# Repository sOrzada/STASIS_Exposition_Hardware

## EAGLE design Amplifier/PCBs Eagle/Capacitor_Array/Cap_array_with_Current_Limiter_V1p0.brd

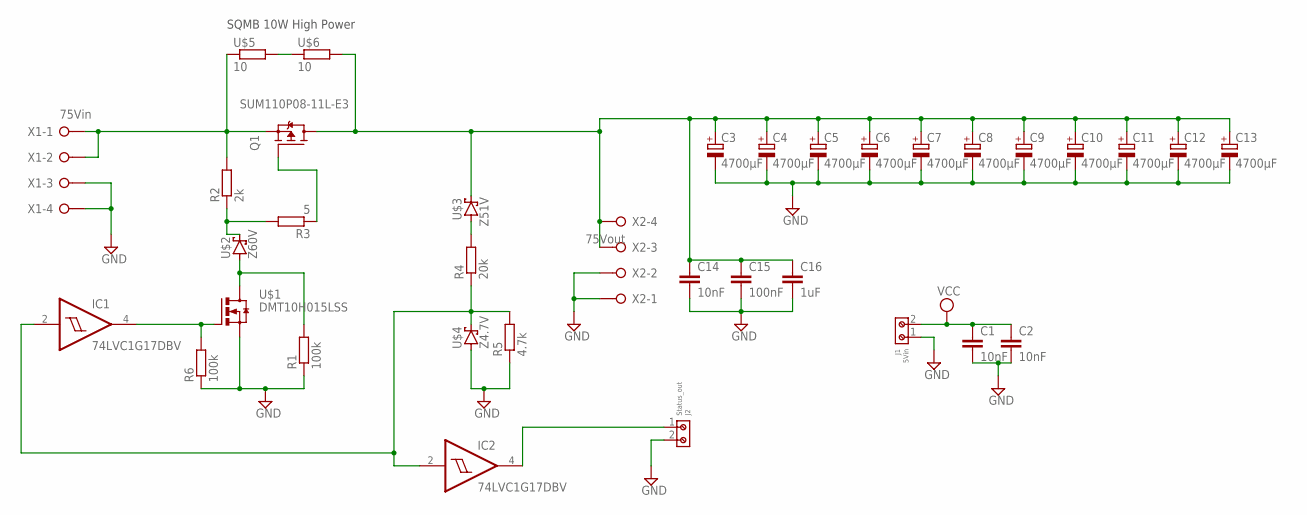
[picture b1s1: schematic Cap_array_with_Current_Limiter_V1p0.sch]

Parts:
C1, C2: 10nF; C0805
C3, C4, C5, C6, C7, C8, C9, C10, C11, C12, C13: 4700µF; EB30D
C14: 10nF; C1206
C15: 100nF; C1206
C16: 1uF; C1206
IC1, IC2: 74LVC1G17DBV; SOT23-5
J1: 5Vin; 691210910002
J2: Status_out; 691210910002
Q1: SUM110P08-11L-E3; TO263
R1, R6: 100k; R0805
R2: 2k; R2512
R3: 5; R0805
R4: 20k; R0805
R5: 4.7k; R0805
U$1: DMT10H015LSS; SOIC8
U$2: Z60V; DO-214AA
U$3: Z51V; DO-214AA
U$4: Z4.7V; DO-214AA
U$5, U$6: 10; SQMB
X1: 75Vin; W237-4P
X2: 75Vout; W237-4P

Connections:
GND: C1.2, C2.2, C3.-, C4.-, C5.-, C6.-, C7.-, C8.-, C9.-, C10.-, C11.-, C12.-, C13.-, C14.2, C15.2, C16.2, IC1.3 (GND), IC2.3 (GND), J1.1, J2.2, R1.1, R5.1, R6.1, U$1.1 (S), U$1.2 (S), U$1.3 (S), U$4.A, X1.3, X1.4, X2.1, X2.2
unnamed: R2.1, R3.2, U$2.C
unnamed: Q1.2 (S), R2.2, U$5.P$1 (1), X1.1, X1.2
unnamed: U$5.P$2 (2), U$6.P$1 (1)
unnamed: IC1.4 (O), R6.2, U$1.4 (G)
unnamed: Q1.1 (G), R3.1
unnamed: C3.+, C4.+, C5.+, C6.+, C7.+, C8.+, C9.+, C10.+, C11.+, C12.+, C13.+, C14.1, C15.1, C16.1, Q1.3 (D), U$3.C, U$6.P$2 (2), X2.3, X2.4
unnamed: R4.2, U$3.A
unnamed: IC1.2 (I), IC2.2 (I), R4.1, R5.2, U$4.C
unnamed: IC2.4 (O), J2.1
unnamed: R1.2, U$1.5 (D), U$1.6 (D), U$1.7 (D), U$1.8 (D), U$2.A
VCC: C1.1, C2.1, IC1.5 (VCC), IC2.5 (VCC), J1.2

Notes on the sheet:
SQMB 10W High Power

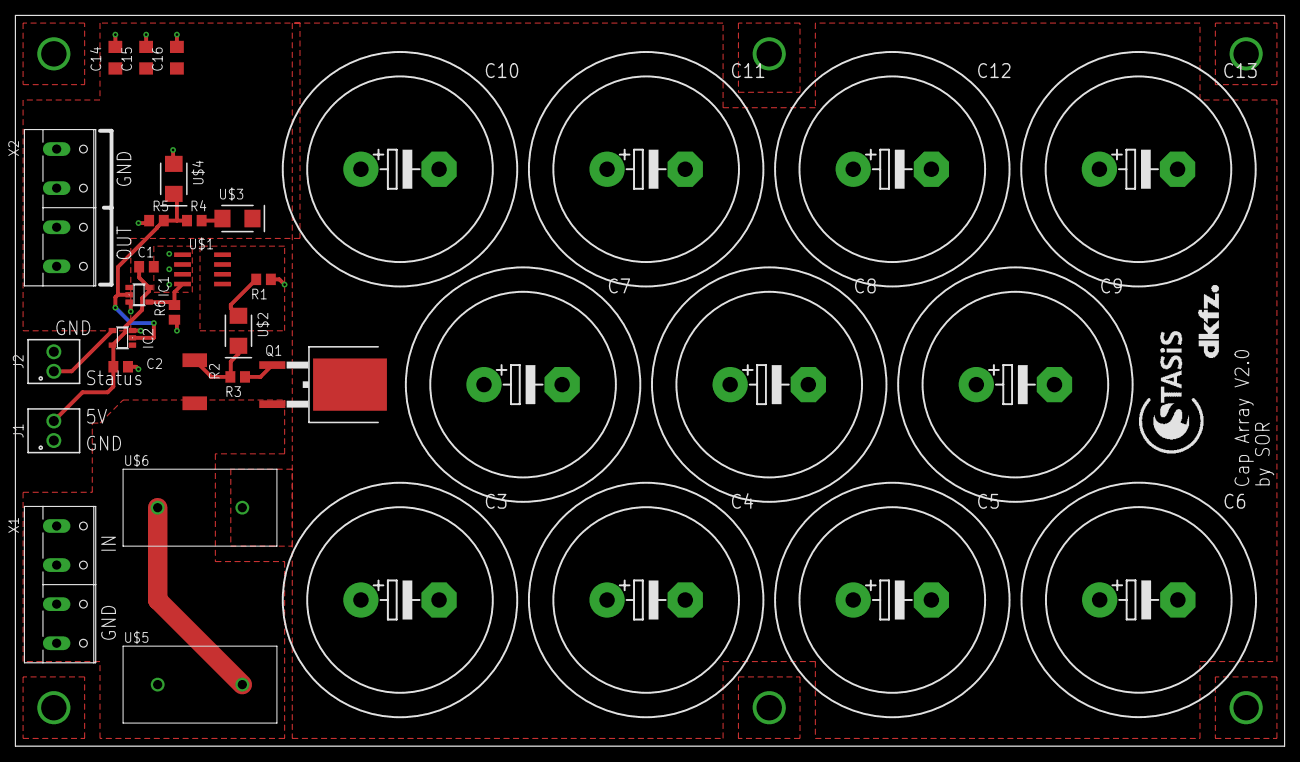
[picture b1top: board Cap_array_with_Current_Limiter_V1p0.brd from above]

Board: 2 copper layers, 165.0 x 95.0 mm, 37 parts (0 on the bottom side), 12 nets.

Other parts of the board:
U$7: LOGO_STASIS
U$8: LOGO_DKFZ

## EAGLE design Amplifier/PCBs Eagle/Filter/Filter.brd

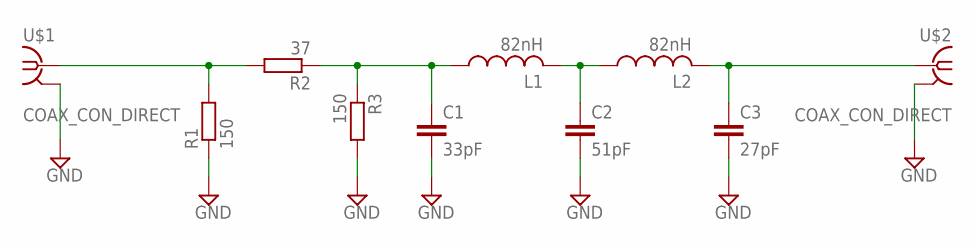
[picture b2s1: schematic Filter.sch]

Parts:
C1: 33pF; C0805
C2: 51pF; C0805
C3: 27pF; C0805
L1, L2: 82nH; L2012C
R1, R3: 150; R0805
R2: 37; R0805
U$1, U$2: COAX_CON_DIRECT; COAX.141

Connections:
GND: C1.2, C2.2, C3.2, R1.1, R3.2, U$1.P$2 (GND), U$2.P$2 (GND)
unnamed: C3.1, L2.2, U$2.P$1 (1)
unnamed: C2.1, L1.2, L2.1
unnamed: C1.1, L1.1, R2.1, R3.1
unnamed: R1.2, R2.2, U$1.P$1 (1)

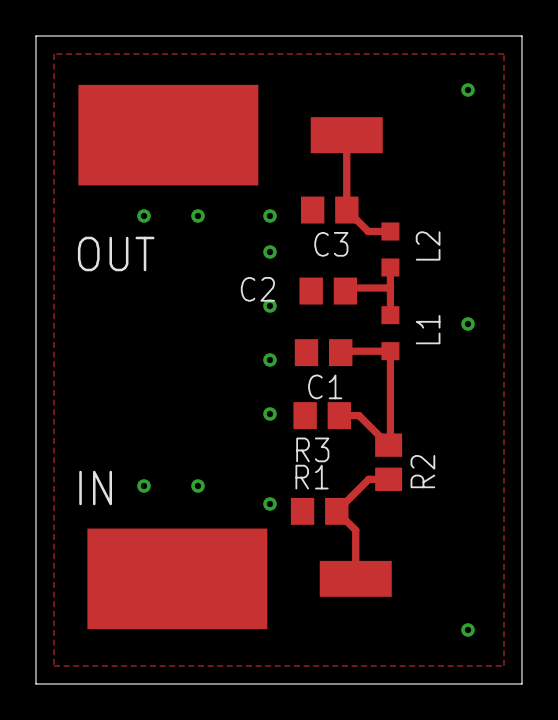
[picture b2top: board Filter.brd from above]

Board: 2 copper layers, 27.0 x 36.0 mm, 10 parts (0 on the bottom side), 5 nets.

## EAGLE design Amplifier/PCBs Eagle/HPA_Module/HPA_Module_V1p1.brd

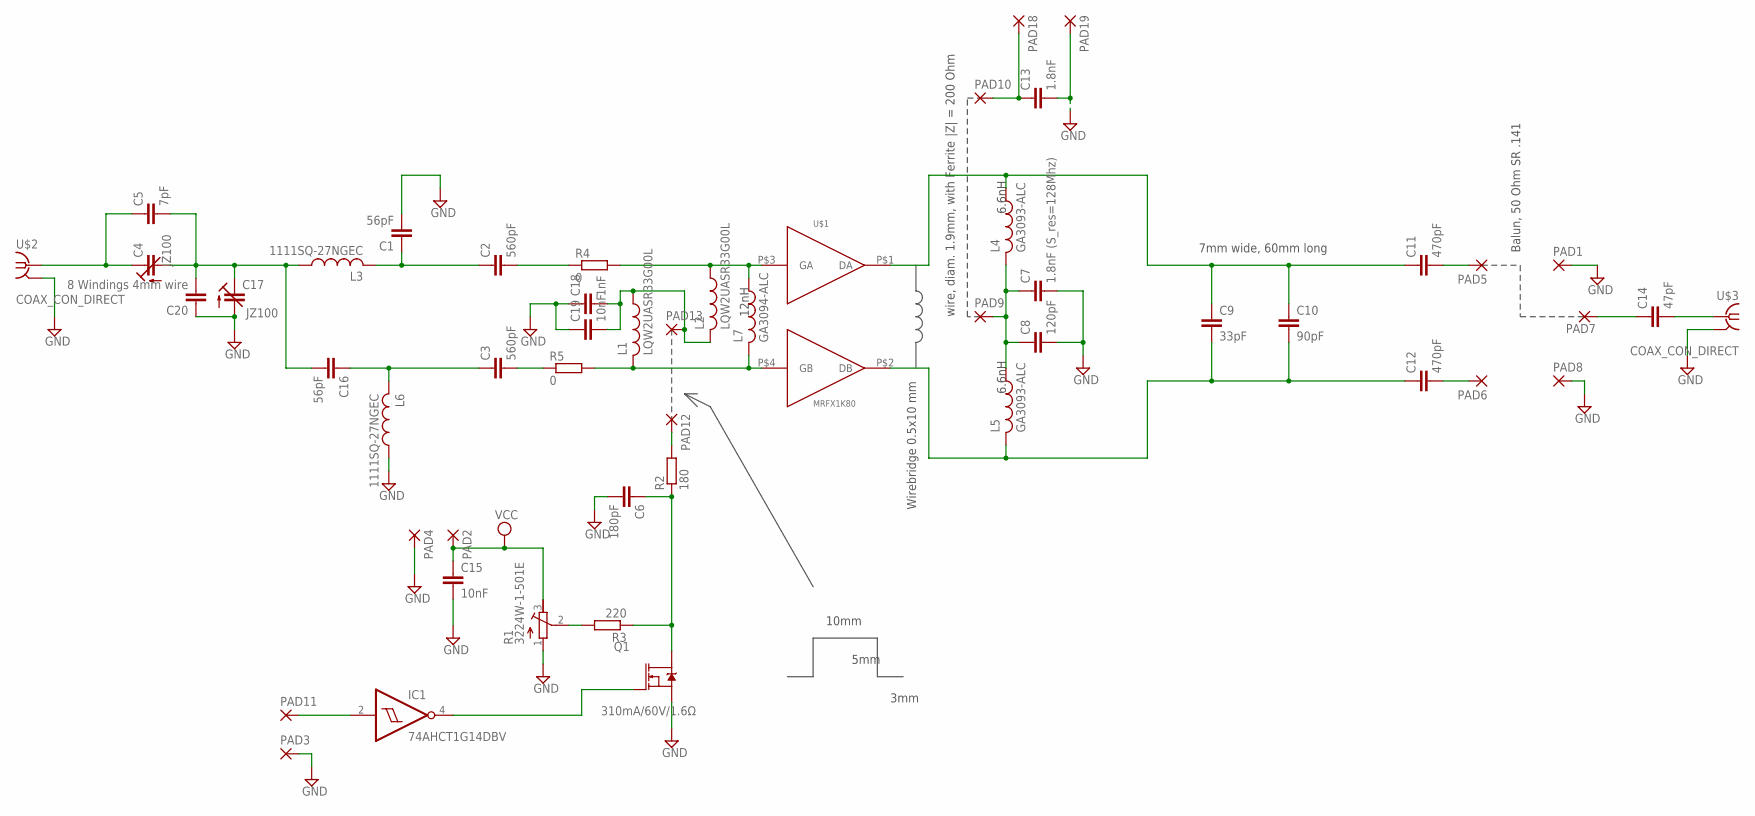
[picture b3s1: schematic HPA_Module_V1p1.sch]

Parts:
C1, C16: 56pF; C1210
C2, C3: 560pF; C1210
C4, C17: JZ100; CTRIM3018_12
C5: 7pF; C1210K
C6: 180pF; C0805
C7: 1.8nF (S_res=128Mhz); C1210
C8: 120pF; C1210
C9: 33pF; C2220K
C10: 90pF; C2220K
C11, C12: 470pF; C1210
C13: 1.8nF; C1210
C14: 47pF; C1210
C15, C19: 10nF; C0805
C18: 1nF; C0805
C20: 8 Windings 4mm wire; C1210K
IC1: 74AHCT1G14DBV; SOT23-5
L1, L2: LQW2UASR33G00L; L2825P
L3, L6: 1111SQ-27NGEC; L2825P
L4, L5: GA3093-ALC; L4532P
L7: GA3094-ALC; L4532P
PAD1, PAD2, PAD3, PAD4, PAD5, PAD6, PAD7, PAD8, PAD9, PAD10, PAD11, PAD12, PAD13, PAD18, PAD19: SMD5; SMD2,54-5,08
Q1: 310mA/60V/1.6Ω; SOT323
R1: 3224W-1-501E; RTRIM3224W
R2: 180; R0805
R3: 220; R0805
R4, R5: 0; R1206
U$1: MRFX1K80; NI-1230H-4S
U$2, U$3: COAX_CON_DIRECT; COAX.141

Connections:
GND: C1.2, C6.2, C7.2, C8.2, C13.2, C15.2, C17.- (A), C18.1, C19.1, C20.1, IC1.3 (GND), L6.1, PAD1.1, PAD3.1, PAD4.1, PAD8.1, PAD19.1, Q1.2 (S), R1.1 (A), U$2.P$2 (GND), U$3.P$2 (GND)
unnamed: L1.2, L7.2, R5.2, U$1.P$4 (GB)
unnamed: L2.1, L7.1, R4.2, U$1.P$3 (GA)
unnamed: C18.2, C19.2, L1.1, L2.2, PAD13.1
unnamed: C9.1, C10.1, C11.1, L4.1, U$1.P$1 (DA)
unnamed: C1.1, C2.1, L3.2
unnamed: C3.1, C16.1, L6.2
unnamed: C4.- (A), C5.2, C16.2, C17.+ (E), C20.2, L3.1
unnamed: C9.2, C10.2, C12.1, L5.2, U$1.P$2 (DB)
unnamed: C4.+ (E), C5.1, U$2.P$1 (1)
unnamed: C7.1, C8.1, L4.2, L5.1, PAD9.1
unnamed: C6.1, Q1.3 (D), R2.1, R3.1
unnamed: C11.2, PAD5.1
unnamed: C12.2, PAD6.1
unnamed: C13.1, PAD10.1, PAD18.1
unnamed: R1.2 (S), R3.2
unnamed: C14.1, PAD7.1
unnamed: C14.2, U$3.P$1 (1)
unnamed: IC1.4 (O), Q1.1 (G)
unnamed: PAD12.1, R2.2
unnamed: IC1.2 (I), PAD11.1
unnamed: C2.2, R4.1
unnamed: C3.2, R5.1
VCC: C15.1, IC1.5 (VCC), PAD2.1, R1.3 (E)

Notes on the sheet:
7mm wide, 60mm long
Balun, 50 Ohm SR .141
wire, diam. 1.9mm, with Ferrite
Wirebridge 0.5x10 mm
10mm
5mm
3mm
|Z| = 200 Ohm
12nH
6.6nH

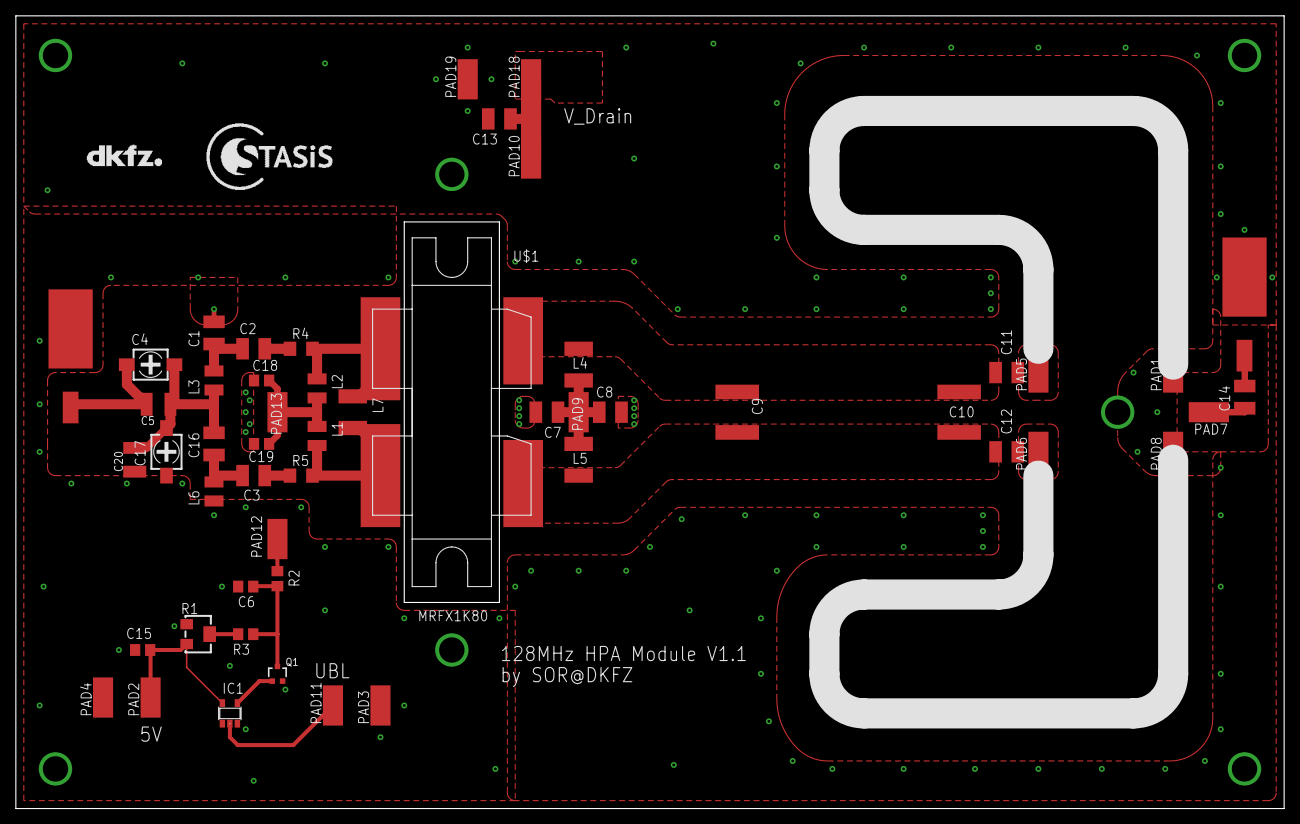
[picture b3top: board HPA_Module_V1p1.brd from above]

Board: 2 copper layers, 160.0 x 100.0 mm, 54 parts (0 on the bottom side), 24 nets.

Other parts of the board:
U$4: LOGO_DKFZ
U$5: LOGO_STASIS

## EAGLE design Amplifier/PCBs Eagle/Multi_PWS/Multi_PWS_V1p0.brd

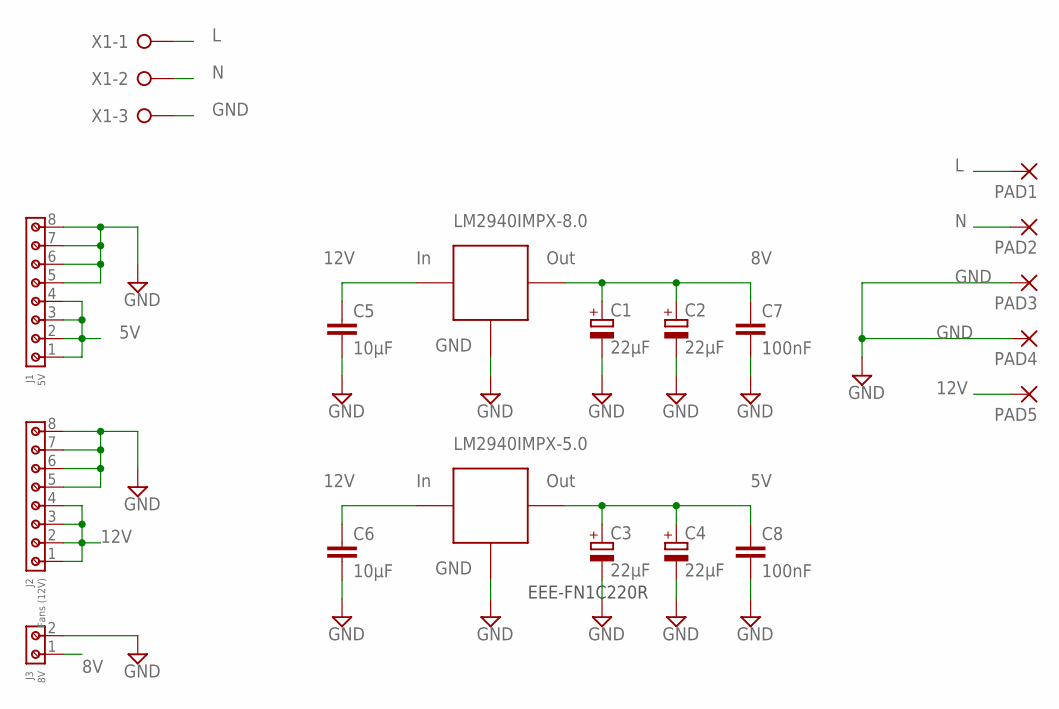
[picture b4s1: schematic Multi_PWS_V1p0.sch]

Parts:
C1, C2, C3, C4: 22µF; PANASONIC_B
C5, C6: 10µF; C1210
C7, C8: 100nF; C1210
J1: 5V; 691210910008
J2: Fans (12V); 691210910008
J3: 8V; 691210910002
PAD1, PAD2, PAD3, PAD4, PAD5: SMD5; SMD2,54-5,08
U$1: LM2940IMPX-8.0; SOT223
U$2: LM2940IMPX-5.0; SOT223
X1: W237-3E

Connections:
5V: C3.+, C4.+, C8.1, J1.1, J1.2, J1.3, J1.4, U$2.3 (VCC)
8V: C1.+, C2.+, C7.1, J3.1, U$1.3 (VCC)
12V: C5.1, C6.1, J2.1, J2.2, J2.3, J2.4, PAD5.1, U$1.1 (IN), U$2.1 (IN)
GND: C1.-, C2.-, C3.-, C4.-, C5.2, C6.2, C7.2, C8.2, J1.5, J1.6, J1.7, J1.8, J2.5, J2.6, J2.7, J2.8, J3.2, PAD3.1, PAD4.1, U$1.2 (GND), U$1.4 (GND), U$2.2 (GND), U$2.4 (GND), X1.3
L: PAD1.1, X1.1
N: PAD2.1, X1.2

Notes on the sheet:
EEE-FN1C220R

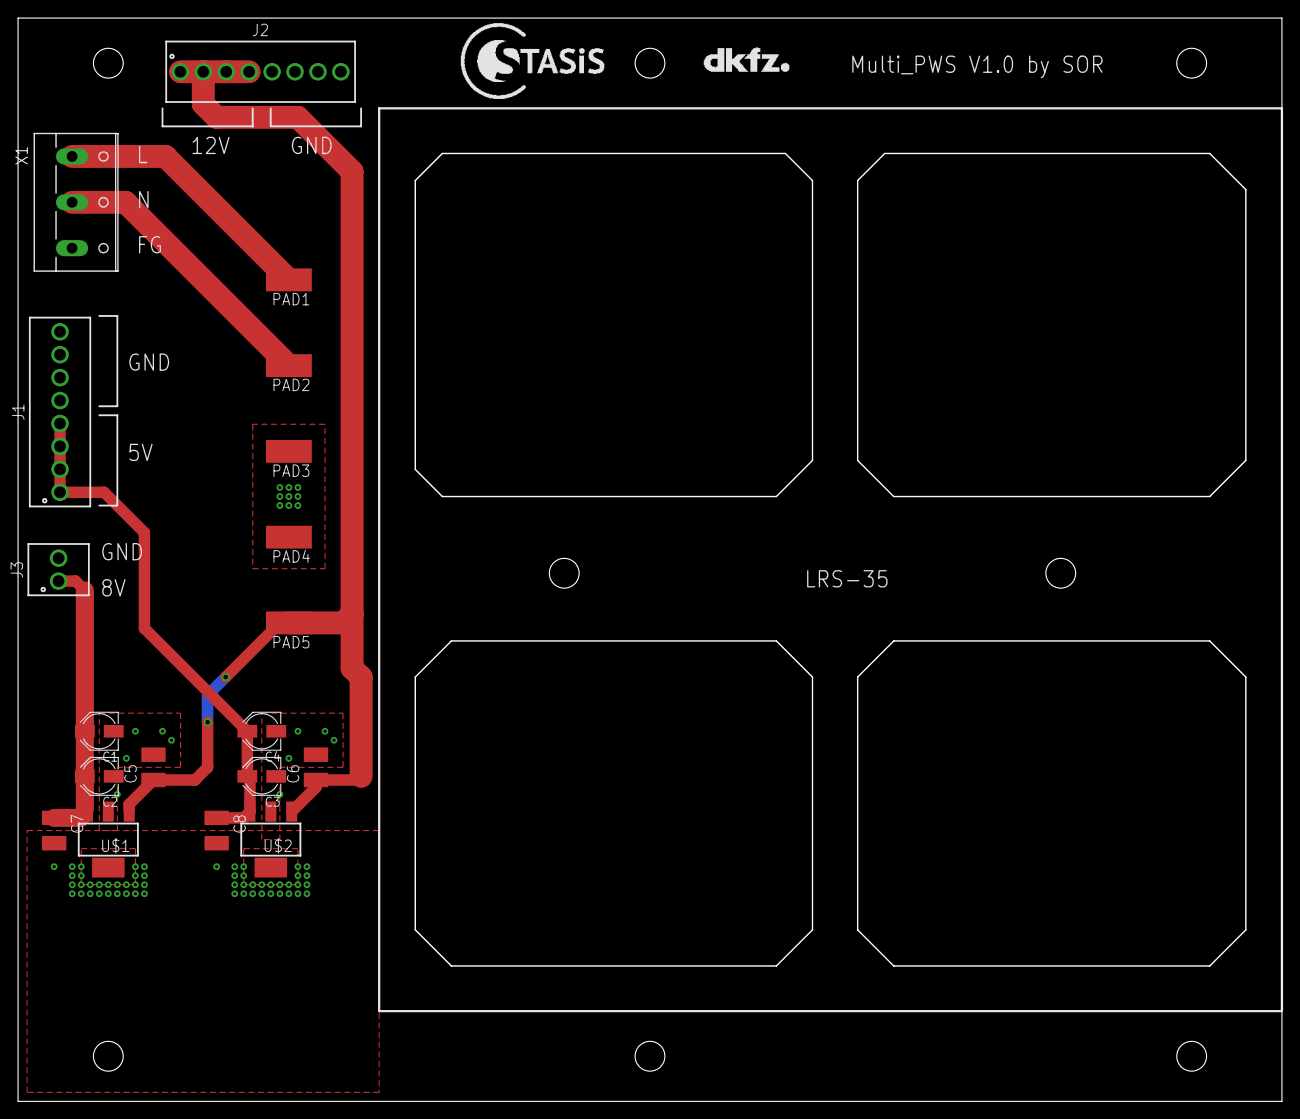
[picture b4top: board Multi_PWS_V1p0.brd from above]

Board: 2 copper layers, 140.0 x 120.0 mm, 21 parts (0 on the bottom side), 6 nets.

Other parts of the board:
U$3: LOGO_DKFZ
U$4: LOGO_STASIS

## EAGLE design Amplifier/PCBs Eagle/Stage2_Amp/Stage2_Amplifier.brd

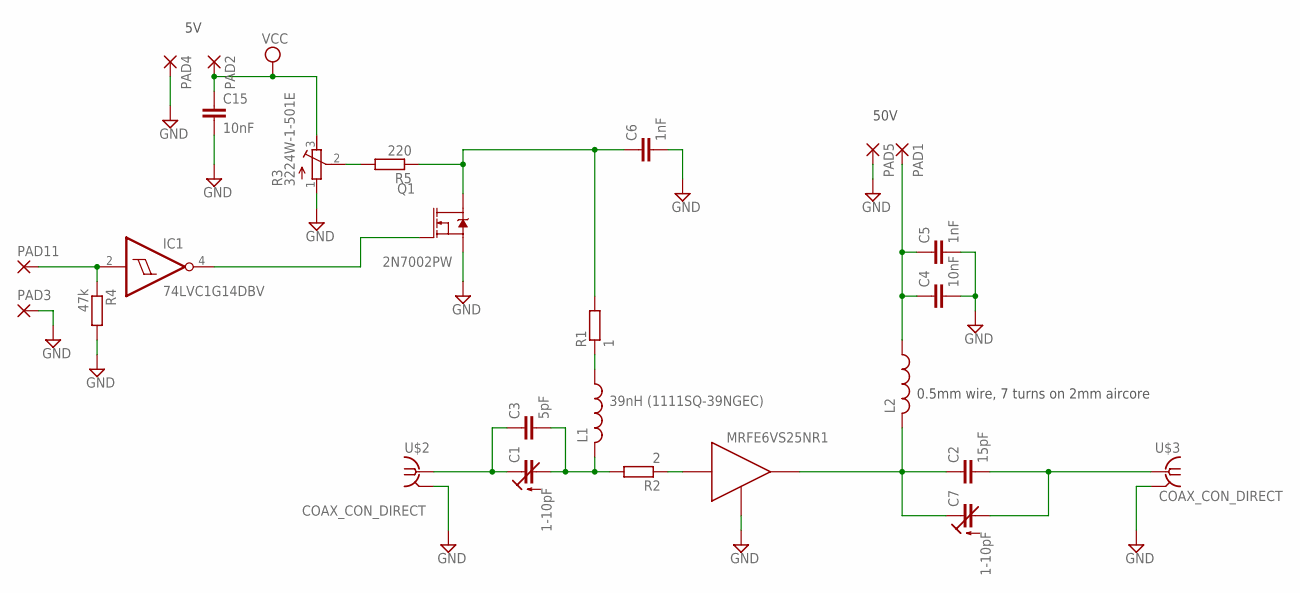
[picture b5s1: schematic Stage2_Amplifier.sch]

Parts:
C1, C7: 1-10pF; CTRIMTZBX4
C2: 15pF; C1210
C3: 5pF; C1210
C4: 10nF; C1206
C5: 1nF; C1206
C6: 1nF; C0805
C15: 10nF; C0805
IC1: 74LVC1G14DBV; SOT23-5
L1: 39nH (1111SQ-39NGEC); L3225P
L2: L-USL3225P; L3225P
PAD1, PAD2, PAD3, PAD4, PAD5, PAD11: SMD5; SMD2,54-5,08
Q1: 2N7002PW; SOT323
R1: 1; R1206
R2: 2; R1206
R3: 3224W-1-501E; RTRIM3224W
R4: 47k; R0805
R5: 220; R0805
U$1: MRFE6VS25NR1; TO-270_ONBOARD
U$2, U$3: COAX_CON_DIRECT; COAX.141

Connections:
GND: C4.2, C5.2, C6.2, C15.2, IC1.3 (GND), PAD3.1, PAD4.1, PAD5.1, Q1.2 (S), R3.1 (A), R4.2, U$1.P$3 (GND), U$2.P$2 (GND), U$3.P$2 (GND)
unnamed: R2.1, U$1.P$2 (IN)
unnamed: C1.2 (A), C3.2, L1.2, R2.2
unnamed: L1.1, R1.1
unnamed: C2.1, C7.1 (E), L2.2, U$1.P$1 (OUT)
unnamed: C1.1 (E), C3.1, U$2.P$1 (1)
unnamed: C2.2, C7.2 (A), U$3.P$1 (1)
unnamed: C4.1, C5.1, L2.1, PAD1.1
unnamed: C6.1, Q1.3 (D), R1.2, R5.1
unnamed: R3.2 (S), R5.2
unnamed: IC1.4 (O), Q1.1 (G)
unnamed: IC1.2 (I), PAD11.1, R4.1
VCC: C15.1, IC1.5 (VCC), PAD2.1, R3.3 (E)

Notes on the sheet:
50V
0.5mm wire, 7 turns on 2mm aircore

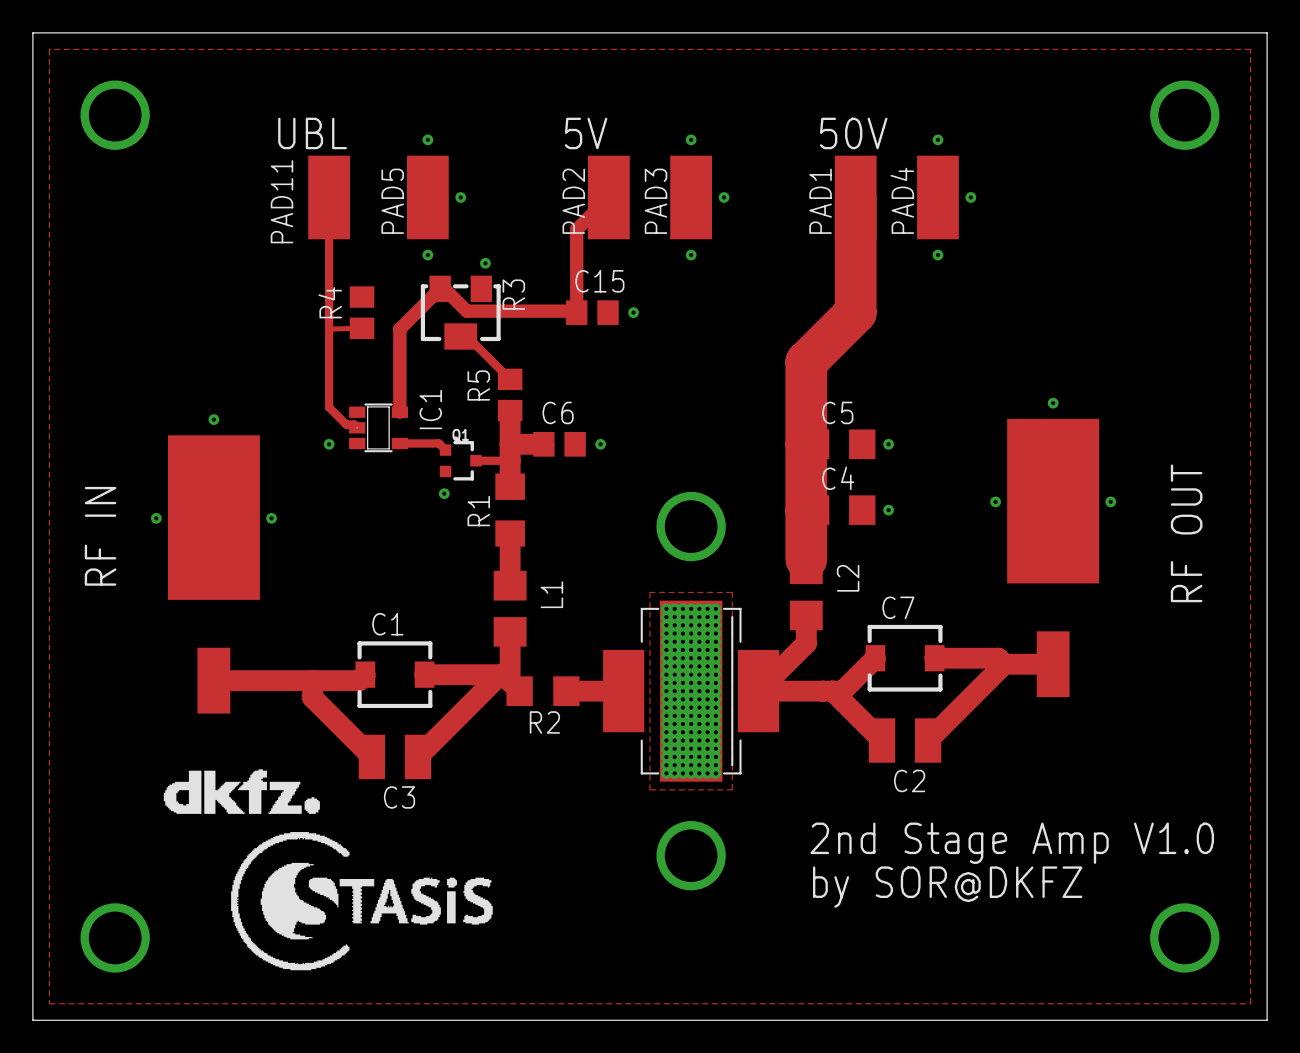
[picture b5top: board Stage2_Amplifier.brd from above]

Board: 2 copper layers, 75.0 x 60.0 mm, 28 parts (0 on the bottom side), 13 nets.

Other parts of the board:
U$4: LOGO_STASIS
U$5: LOGO_DKFZ

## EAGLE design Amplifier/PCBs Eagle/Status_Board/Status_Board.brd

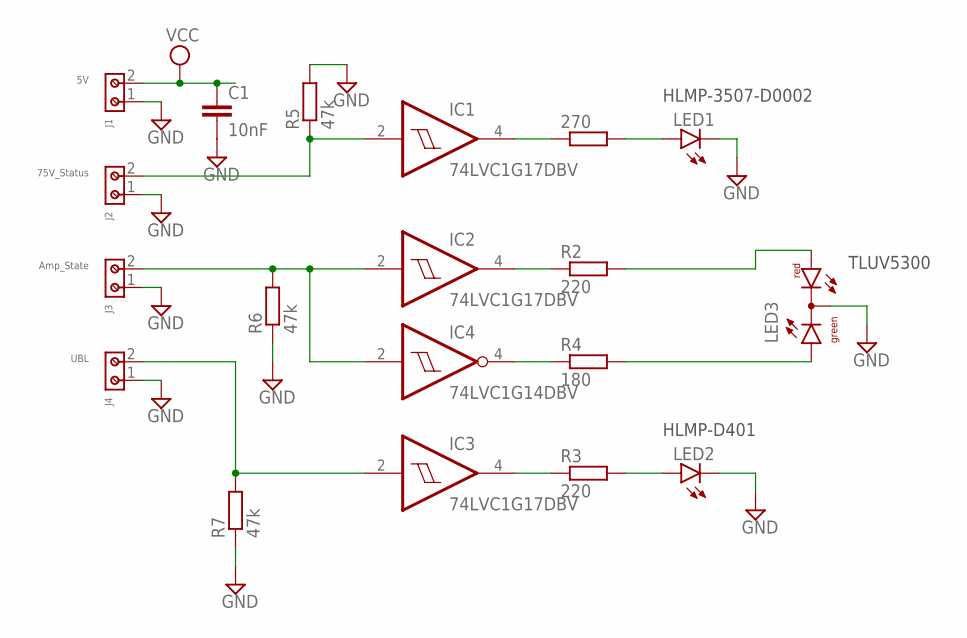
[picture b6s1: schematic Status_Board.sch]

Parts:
270: R-EU_R0805; R0805
C1: 10nF; C0805
IC1, IC2, IC3: 74LVC1G17DBV; SOT23-5
IC4: 74LVC1G14DBV; SOT23-5
J1: 5V; 691210910002
J2: 75V_Status; 691210910002
J3: Amp_State; 691210910002
J4: UBL; 691210910002
LED1, LED2: LED5MM
LED3: DUOLED-RG-C; DUOLED-C-5MM
R2, R3: 220; R0805
R4: 180; R0805
R5, R6, R7: 47k; R0805

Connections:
GND: C1.2, IC1.3 (GND), IC2.3 (GND), IC3.3 (GND), IC4.3 (GND), J1.1, J2.1, J3.1, J4.1, LED1.K (C), LED2.K (C), LED3.C, R5.2, R6.1, R7.1
unnamed: IC4.4 (O), R4.1
unnamed: IC1.2 (I), J2.2, R5.1
unnamed: IC2.2 (I), IC4.2 (I), J3.2, R6.2
unnamed: IC3.2 (I), J4.2, R7.2
unnamed: 270.1, IC1.4 (O)
unnamed: IC2.4 (O), R2.1
unnamed: IC3.4 (O), R3.1
unnamed: 270.2, LED1.A
unnamed: LED3.AR, R2.2
unnamed: LED2.A, R3.2
unnamed: LED3.AX (AG), R4.2
VCC: C1.1, IC1.5 (VCC), IC2.5 (VCC), IC3.5 (VCC), IC4.5 (VCC), J1.2

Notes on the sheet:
TLUV5300
HLMP-3507-D0002
HLMP-D401

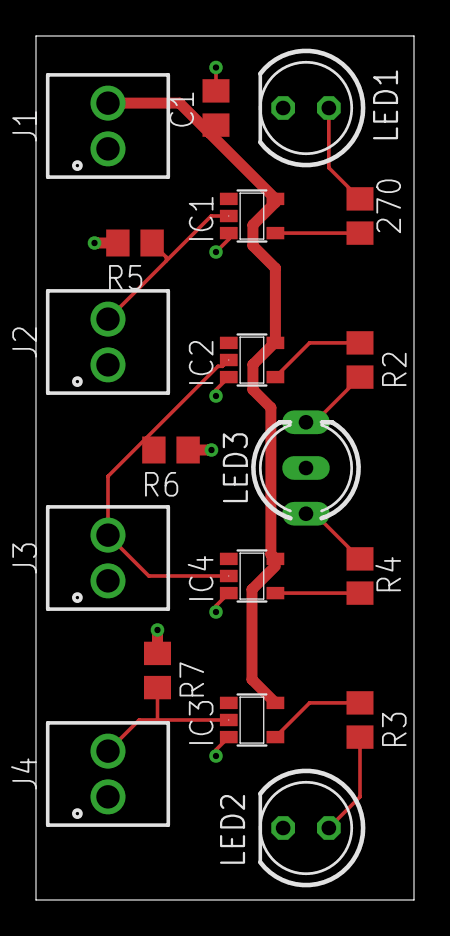
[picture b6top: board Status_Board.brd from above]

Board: 2 copper layers, 21.0 x 48.0 mm, 19 parts (0 on the bottom side), 13 nets.

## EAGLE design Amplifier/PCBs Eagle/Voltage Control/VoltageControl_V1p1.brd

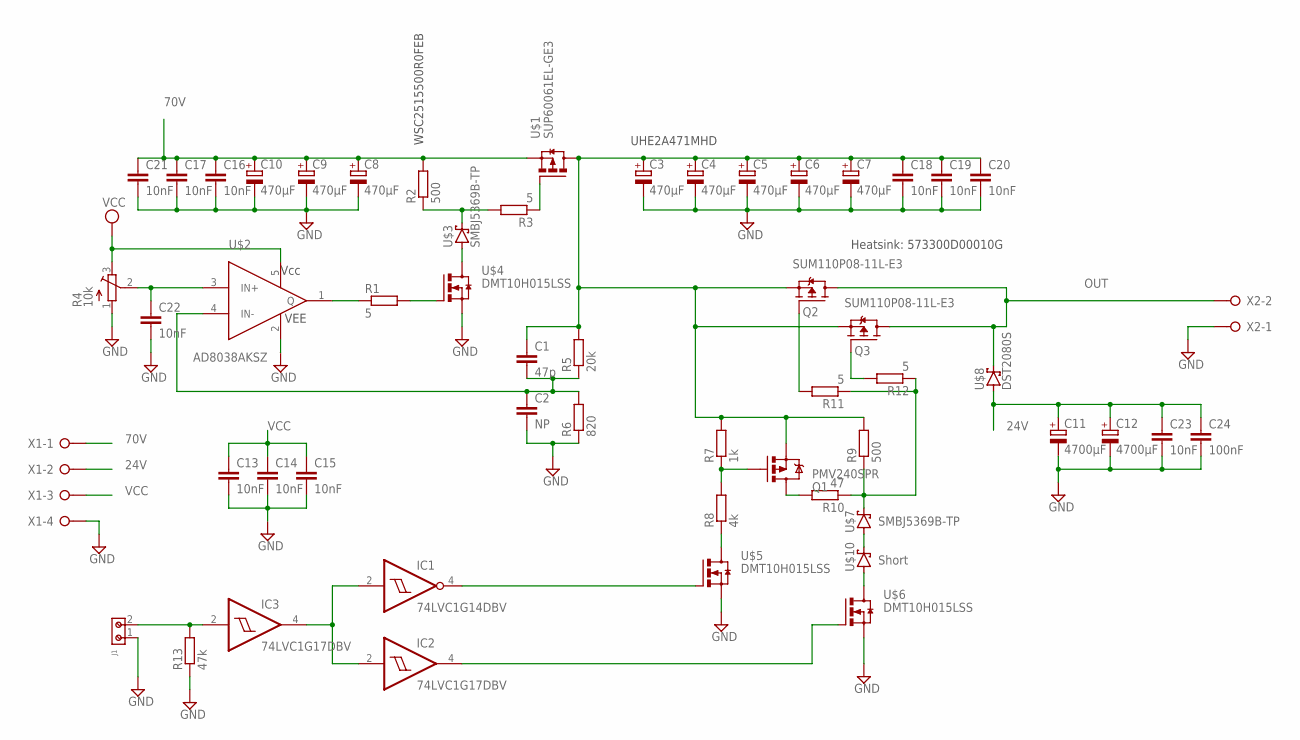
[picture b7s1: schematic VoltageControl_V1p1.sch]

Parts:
C1: 47p; C0805
C2: NP; C0805
C3, C4, C5, C6, C7, C8, C9, C10: 470µF; E7,5-16
C11, C12: 4700µF; E7,5-18
C13, C14, C15, C16, C17, C18, C19, C20, C21, C22: 10nF; C0805
C23: 10nF; C1206
C24: 100nF; C1206
IC1: 74LVC1G14DBV; SOT23-5
IC2, IC3: 74LVC1G17DBV; SOT23-5
J1: 691210910002
Q1: PMV240SPR; SOT23-3
Q2, Q3: SUM110P08-11L-E3; TO263
R1, R3, R11, R12: 5; R0805
R2, R9: 500; R2512
R4: 10k; SM-42/43X
R5: 20k; R0805
R6: 820; R0805
R7: 1k; R2512
R8: 4k; R2512
R10: 47; R0805
R13: 47k; R0805
U$1: SUP60061EL-GE3; TO220BH
U$2: AD8038AKSZ; SC70-5
U$3, U$7: SMBJ5369B-TP; DO-214AA
U$4, U$5, U$6: DMT10H015LSS; SOIC8
U$8: DST2080S; TO-277B
U$10: Short; DO-214AA
X1: W237-04P; W237-4P
X2: W237-02P; W237-132

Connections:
24V: C11.+, C12.+, C23.1, C24.1, U$8.P$2 (A), U$8.P$3 (A), X1.2
70V: C8.+, C9.+, C10.+, C16.1, C17.1, C21.1, R2.2, U$1.P$3 (S), X1.1
GND: C2.2, C3.-, C4.-, C5.-, C6.-, C7.-, C8.-, C9.-, C10.-, C11.-, C12.-, C13.2, C14.2, C15.2, C16.2, C17.2, C18.2, C19.2, C20.2, C21.2, C22.2, C23.2, C24.2, IC1.3 (GND), IC2.3 (GND), IC3.3 (GND), J1.1, R4.1 (A), R6.1, R13.1, U$2.2 (VEE), U$4.1 (S), U$4.2 (S), U$4.3 (S), U$5.1 (S), U$5.2 (S), U$5.3 (S), U$6.1 (S), U$6.2 (S), U$6.3 (S), X1.4, X2.1
unnamed: R1.1, U$2.1 (Q)
unnamed: R1.2, U$4.4 (G)
unnamed: U$3.A, U$4.5 (D), U$4.6 (D), U$4.7 (D), U$4.8 (D)
unnamed: R2.1, R3.2, U$3.C
unnamed: R3.1, U$1.P$1 (G)
unnamed: U$7.A, U$10.C
unnamed: C22.1, R4.2 (S), U$2.3 (IN+)
unnamed: C1.2, C2.1, R5.1, R6.2, U$2.4 (IN-)
unnamed: Q1.1 (G), R7.1, R8.2
unnamed: C1.1, C3.+, C4.+, C5.+, C6.+, C7.+, C18.1, C19.1, C20.1, Q1.2 (S), Q2.2 (S), Q3.2 (S), R5.2, R7.2, R9.2, U$1.P$2 (D)
unnamed: IC2.4 (O), U$6.4 (G)
unnamed: R8.1, U$5.5 (D), U$5.6 (D), U$5.7 (D), U$5.8 (D)
unnamed: U$6.5 (D), U$6.6 (D), U$6.7 (D), U$6.8 (D), U$10.A
unnamed: R9.1, R10.1, R11.1, R12.1, U$7.C
unnamed: Q1.3 (D), R10.2
unnamed: Q2.1 (G), R11.2
unnamed: Q3.1 (G), R12.2
unnamed: IC1.2 (I), IC2.2 (I), IC3.4 (O)
unnamed: IC1.4 (O), U$5.4 (G)
unnamed: IC3.2 (I), J1.2, R13.2
OUT: Q2.3 (D), Q3.3 (D), U$8.P$1 (C), X2.2
VCC: C13.1, C14.1, C15.1, IC1.5 (VCC), IC2.5 (VCC), IC3.5 (VCC), R4.3 (E), U$2.5 (VCC), X1.3

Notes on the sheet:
WSC2515500R0FEB
UHE2A471MHD
Heatsink: 573300D00010G

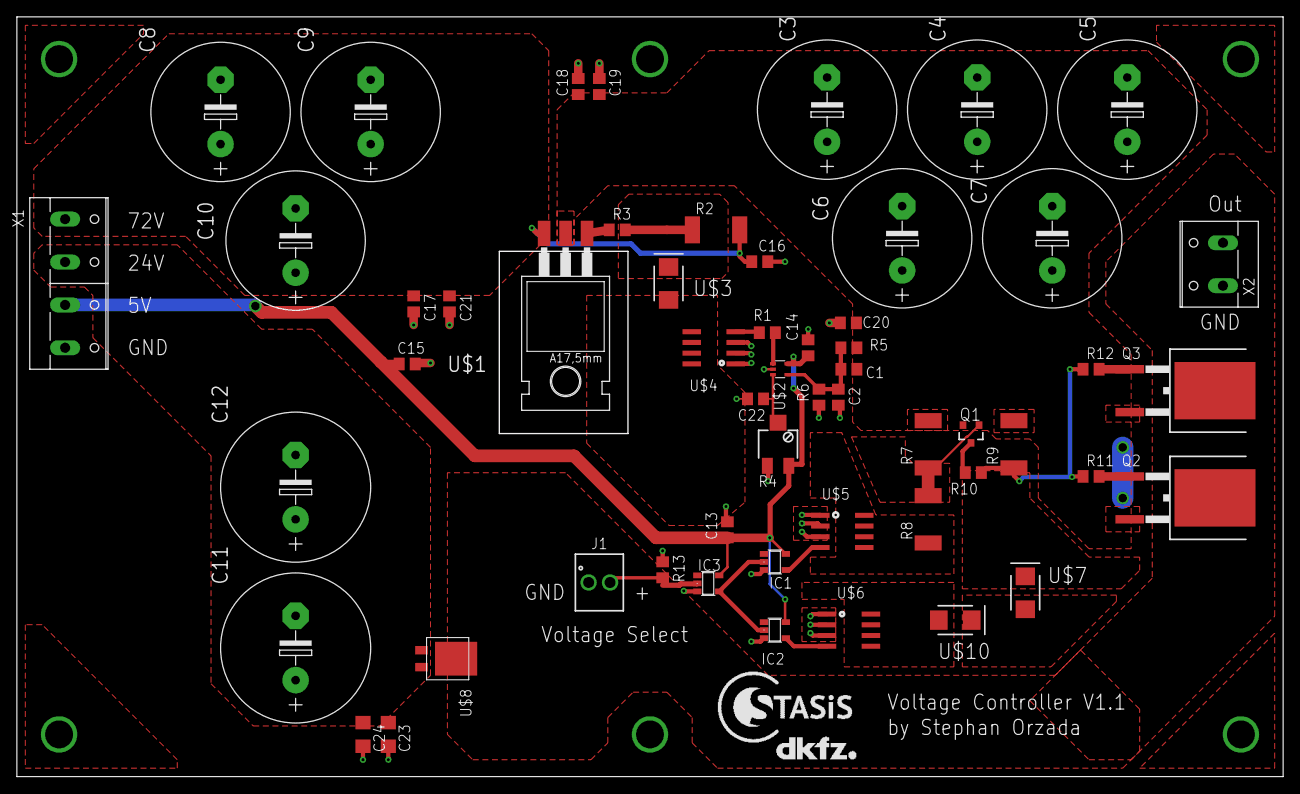
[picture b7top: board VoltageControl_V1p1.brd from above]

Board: 2 copper layers, 150.0 x 90.0 mm, 57 parts (0 on the bottom side), 25 nets.

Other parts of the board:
U$11: LOGO_STASIS
U$12: LOGO_DKFZ

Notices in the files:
parts and their libraries:
Wurth_Connectors_WR-TBL Rising Cage Clam: Copyright: Würth Elektronik
SparkFun-DiscreteSemi: Licensing: Creative Commons ShareAlike 4.0 International - https://creativecommons.org/licenses/by-sa/4.0
